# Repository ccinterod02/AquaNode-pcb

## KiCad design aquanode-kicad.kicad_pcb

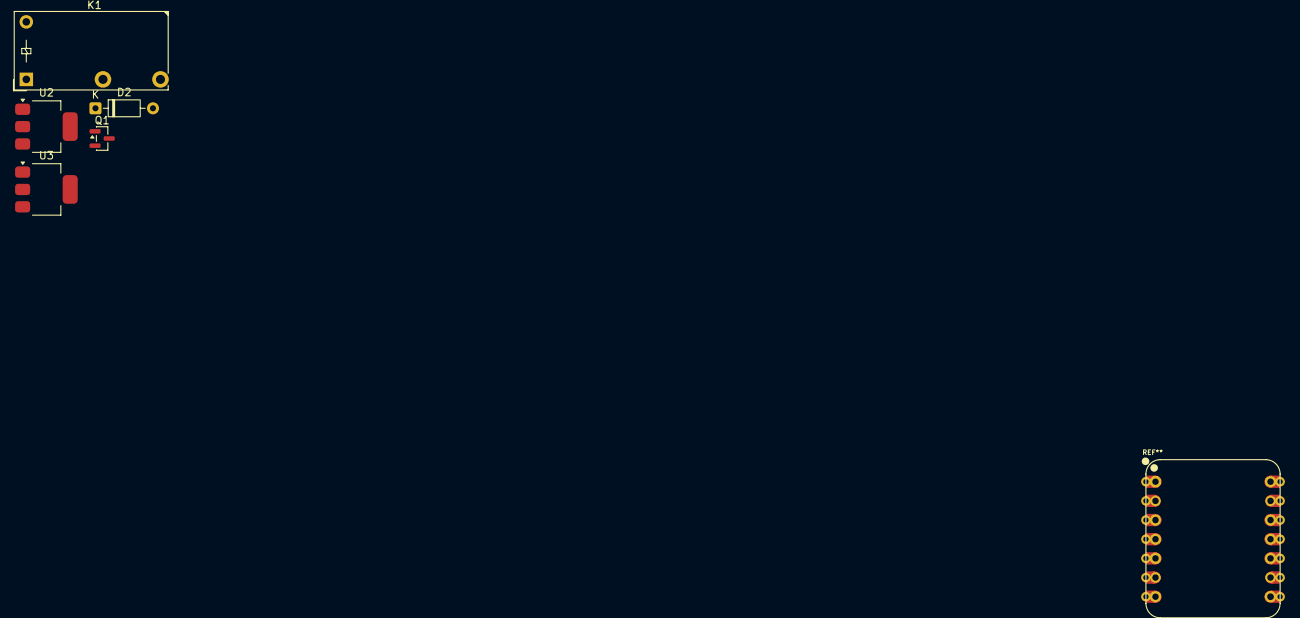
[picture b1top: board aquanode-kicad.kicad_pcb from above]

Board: 2 copper layers, 5 parts (0 on the bottom side), 3 nets, no tracks yet.

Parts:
D2: 1N4148; D_DO-35_SOD27_P7.62mm_Horizontal
K1: RM50-xx21; Relay_SPST_Finder_32.21-x300
Q1: BC817; SOT-23
U2: AMS1117-3.3; SOT-223-3_TabPin2
U3: AMS1117-5.0; SOT-223-3_TabPin2

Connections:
+12V: D2.1 (K), K1.11, K1.A2, U2.3 (VI), U3.3 (VI)
GND: Q1.2 (E), U2.1 (GND), U3.1 (GND)
r: D2.2 (A), K1.A1, Q1.3 (C)

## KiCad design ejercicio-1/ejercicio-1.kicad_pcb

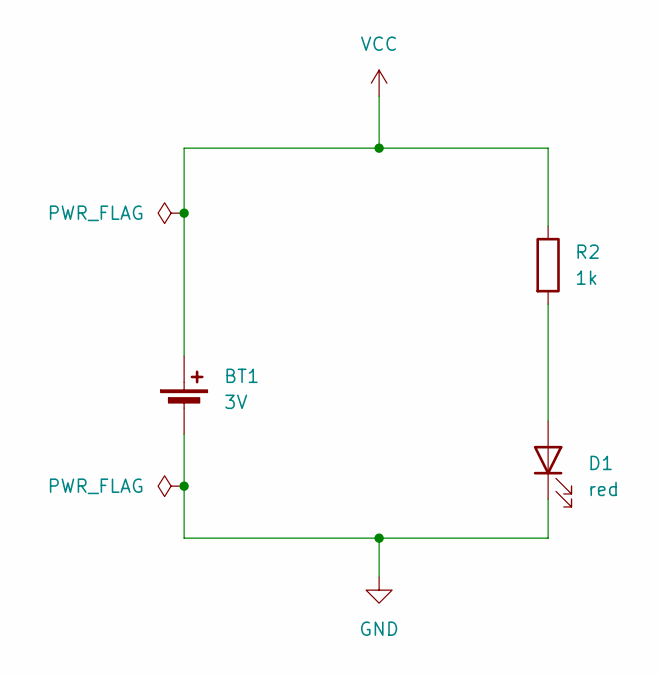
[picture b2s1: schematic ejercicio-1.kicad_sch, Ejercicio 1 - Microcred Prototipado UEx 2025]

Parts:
BT1: 3V; BatteryHolder_Keystone_1058_1x2032
D1: red; LED_D5.0mm
R2: 1k; R_Axial_DIN0309_L9.0mm_D3.2mm_P12.70mm_Horizontal

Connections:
GND: BT1.2 (-), D1.1 (K)
unnamed: D1.2 (A), R2.2
VCC: BT1.1 (+), R2.1

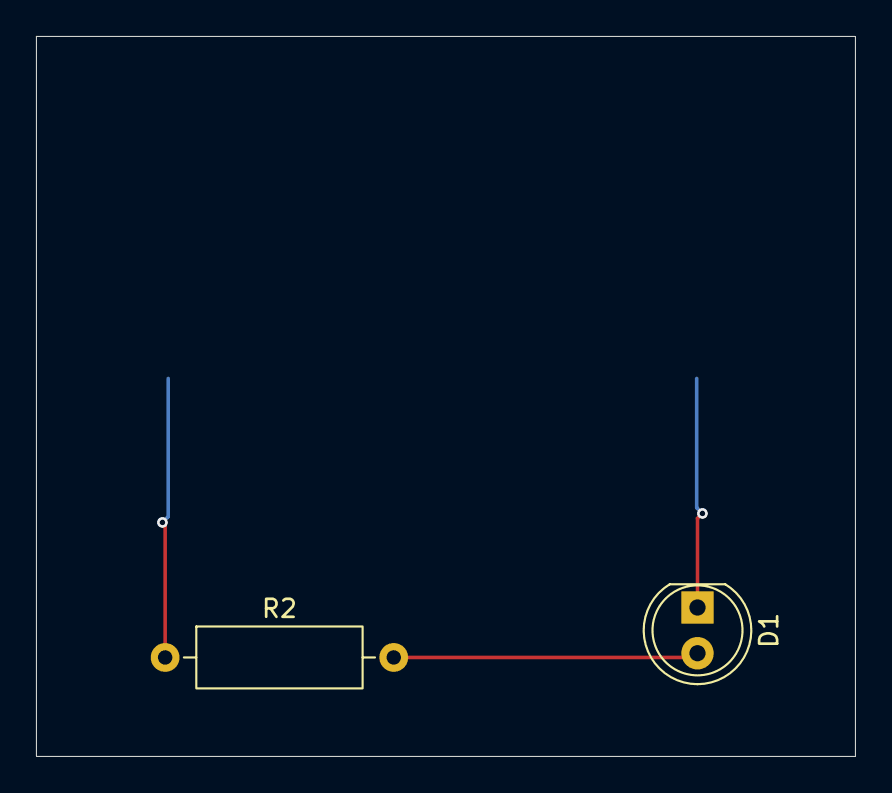
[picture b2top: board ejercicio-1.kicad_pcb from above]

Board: 2 copper layers, 45.5 x 40.0 mm, 3 parts (1 on the bottom side), 3 nets.

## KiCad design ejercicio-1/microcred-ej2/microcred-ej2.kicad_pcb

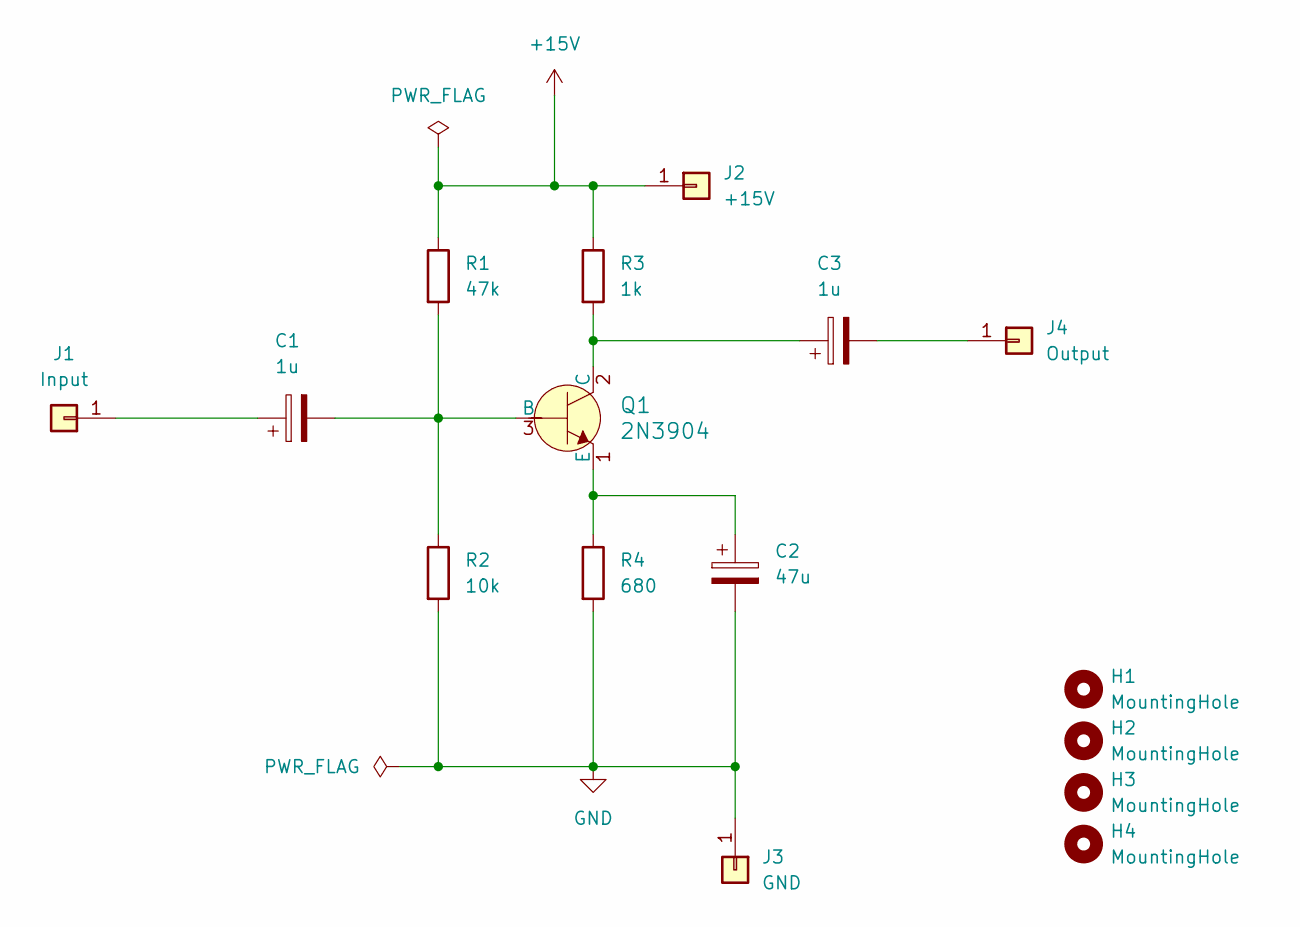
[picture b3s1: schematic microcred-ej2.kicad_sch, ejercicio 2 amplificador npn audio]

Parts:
C1, C3: 1u; CP_Radial_D7.5mm_P2.50mm
C2: 47u; CP_Radial_D7.5mm_P2.50mm
H1, H2, H3, H4: MountingHole; MountingHole_2.5mm_Pad
J1: Input; PinHeader_1x01_P2.54mm_Vertical
J2: +15V; PinHeader_1x01_P2.54mm_Vertical
J3: GND; PinHeader_1x01_P2.54mm_Vertical
J4: Output; PinHeader_1x01_P2.54mm_Vertical
Q1: 2N3904; TO-92L_Inline; MPN 2N3904; Digi-Key_PN 2N3904CS-ND
R1: 47k; R_Axial_DIN0207_L6.3mm_D2.5mm_P2.54mm_Vertical
R2: 10k; R_Axial_DIN0207_L6.3mm_D2.5mm_P2.54mm_Vertical
R3: 1k; R_Axial_DIN0207_L6.3mm_D2.5mm_P2.54mm_Vertical
R4: 680; R_Axial_DIN0207_L6.3mm_D2.5mm_P2.54mm_Vertical

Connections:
+15V: J2.1, R1.1, R3.1
GND: C2.2, J3.1, R2.2, R4.2
unnamed: C1.1, J1.1
unnamed: C3.2, J4.1
unnamed: C1.2, Q1.3 (B), R1.2, R2.1
unnamed: C3.1, Q1.2 (C), R3.2
unnamed: C2.1, Q1.1 (E), R4.1

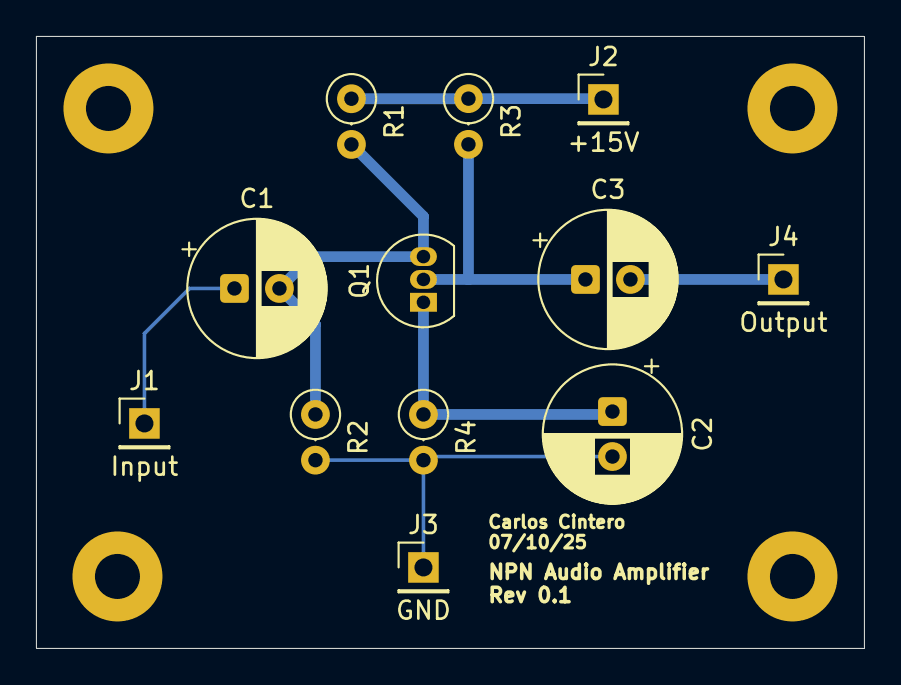
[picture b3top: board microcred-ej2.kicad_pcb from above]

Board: 2 copper layers, 46.0 x 34.0 mm, 16 parts (0 on the bottom side), 7 nets.

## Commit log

2025-10-14 primer commit
2025-10-14 arreglado pro
2025-10-14 asignar huellas
2025-10-14 huellas
